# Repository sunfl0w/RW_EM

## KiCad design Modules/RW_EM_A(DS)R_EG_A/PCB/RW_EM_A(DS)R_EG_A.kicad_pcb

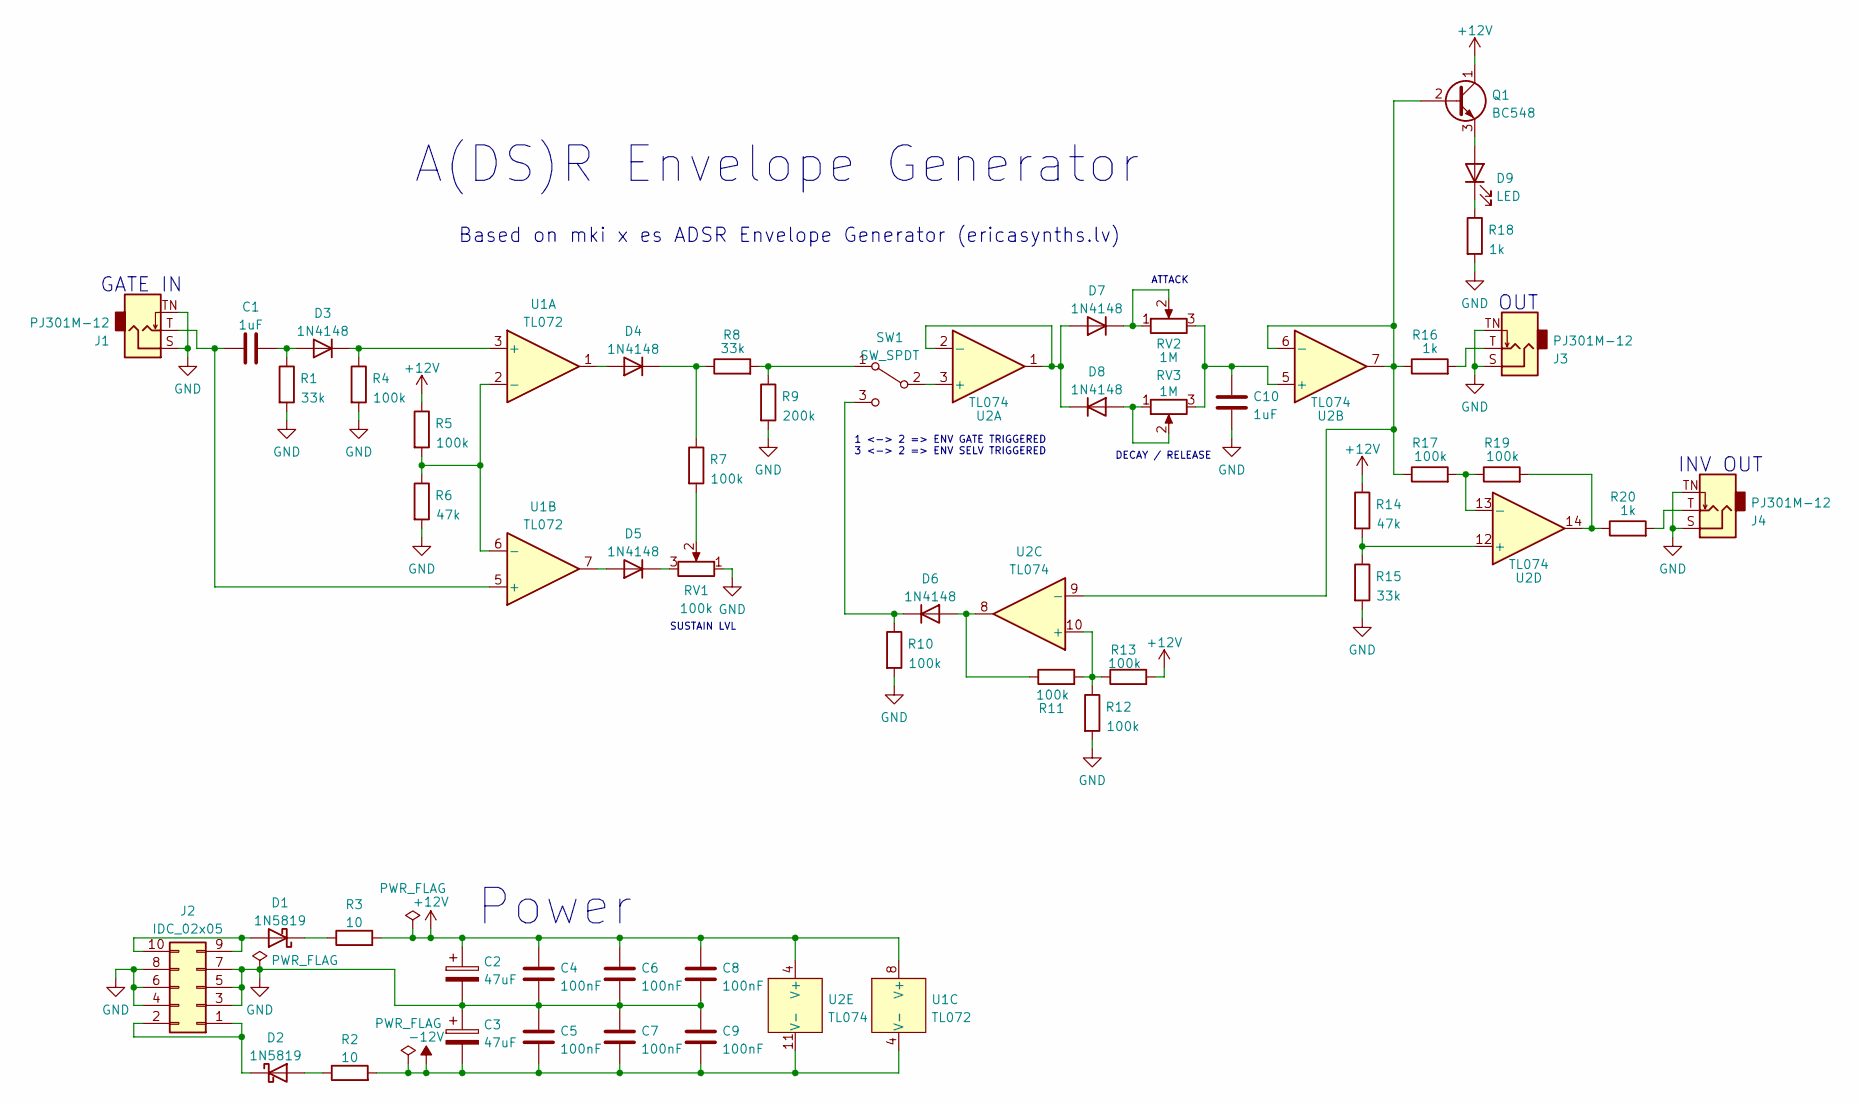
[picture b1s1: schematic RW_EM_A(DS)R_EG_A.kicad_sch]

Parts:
C1, C10: 1uF; C_Rect_L7.2mm_W3.5mm_P5.00mm_FKS2_FKP2_MKS2_MKP2
C2, C3: 47uF; CP_Radial_D5.0mm_P2.00mm
C4, C5, C6, C7, C8, C9: 100nF; C_Disc_D5.0mm_W2.5mm_P5.00mm
D1, D2: 1N5819; D_DO-41_SOD81_P10.16mm_Horizontal
D3, D4, D5, D6, D7, D8: 1N4148; D_DO-35_SOD27_P7.62mm_Horizontal
D9: LED; LED_D5.0mm
J1, J3, J4: PJ301M-12
J2: IDC_02x05; IDC-Header_2x05_P2.54mm_Vertical
Q1: BC548; TO-92_Inline
R1, R8, R15: 33k; R_Axial_DIN0207_L6.3mm_D2.5mm_P2.54mm_Vertical
R2, R3: 10; R_Axial_DIN0207_L6.3mm_D2.5mm_P10.16mm_Horizontal
R4, R5, R7, R10, R11, R12, R13, R17, R19: 100k; R_Axial_DIN0207_L6.3mm_D2.5mm_P2.54mm_Vertical
R6, R14: 47k; R_Axial_DIN0207_L6.3mm_D2.5mm_P2.54mm_Vertical
R9: 200k; R_Axial_DIN0207_L6.3mm_D2.5mm_P2.54mm_Vertical
R16, R18, R20: 1k; R_Axial_DIN0207_L6.3mm_D2.5mm_P10.16mm_Horizontal
RV1: 100k; Potentiometer_R0904N_SongHuei
RV2, RV3: 1M; Potentiometer_R0904N_SongHuei
SW1: SW_SPDT; Toggle_Switch_PINS_SPDT
U1: TL072; DIP-8_W7.62mm
U2: TL074; DIP-14_W7.62mm

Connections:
+12V: C2.1, C4.1, C6.1, C8.1, Q1.1 (C), R3.2, R5.1, R13.2, R14.1, U1.8 (V+), U2.4 (V+)
-12V: C3.2, C5.2, C7.2, C9.2, R2.2, U1.4 (V-), U2.11 (V-)
GND: C2.2, C3.1, C4.2, C5.1, C6.2, C7.1, C8.2, C9.1, C10.1, J1.S, J1.TN, J2.3, J2.4, J2.5, J2.6, J2.7, J2.8, J3.S, J3.TN, J4.S, J4.TN, R1.2, R4.2, R6.2, R9.2, R10.2, R12.2, R15.2, R18.2, RV1.1
unnamed: C1.1, J1.T, U1.5 (+)
unnamed: C1.2, D3.2 (A), R1.1
unnamed: C10.2, RV2.3, RV3.3, U2.5 (+)
unnamed: D1.1 (K), R3.1
unnamed: D1.2 (A), J2.9, J2.10
unnamed: D2.1 (K), J2.1, J2.2
unnamed: D2.2 (A), R2.1
unnamed: D3.1 (K), R4.1, U1.3 (+)
unnamed: D4.1 (K), R7.1, R8.1
unnamed: D4.2 (A), U1.1
unnamed: D5.1 (K), RV1.3
unnamed: D5.2 (A), U1.7
unnamed: D6.1 (K), R10.1, SW1.3 (C)
unnamed: D6.2 (A), R11.1, U2.8
unnamed: D7.1 (K), RV2.1, RV2.2
unnamed: D7.2 (A), D8.1 (K), U2.1, U2.2 (-)
unnamed: D8.2 (A), RV3.1, RV3.2
unnamed: D9.1 (K), R18.1
unnamed: D9.2 (A), Q1.3 (E)
unnamed: J3.T, R16.2
unnamed: J4.T, R20.2
unnamed: Q1.2 (B), R16.1, R17.1, U2.6 (-), U2.7, U2.9 (-)
unnamed: R5.2, R6.1, U1.2 (-), U1.6 (-)
unnamed: R7.2, RV1.2
unnamed: R8.2, R9.1, SW1.1 (A)
unnamed: R11.2, R12.1, R13.1, U2.10 (+)
unnamed: R14.2, R15.1, U2.12 (+)
unnamed: R17.2, R19.1, U2.13 (-)
unnamed: R19.2, R20.1, U2.14
unnamed: SW1.2 (B), U2.3 (+)

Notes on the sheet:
INV OUT
SUSTAIN LVL
1 <-> 2 => ENV GATE TRIGGERED 3 <-> 2 => ENV SELV TRIGGERED
OUT
A(DS)R Envelope Generator
DECAY / RELEASE
ATTACK
GATE IN
Based on mki x es ADSR Envelope Generator (ericasynths.lv)
Power

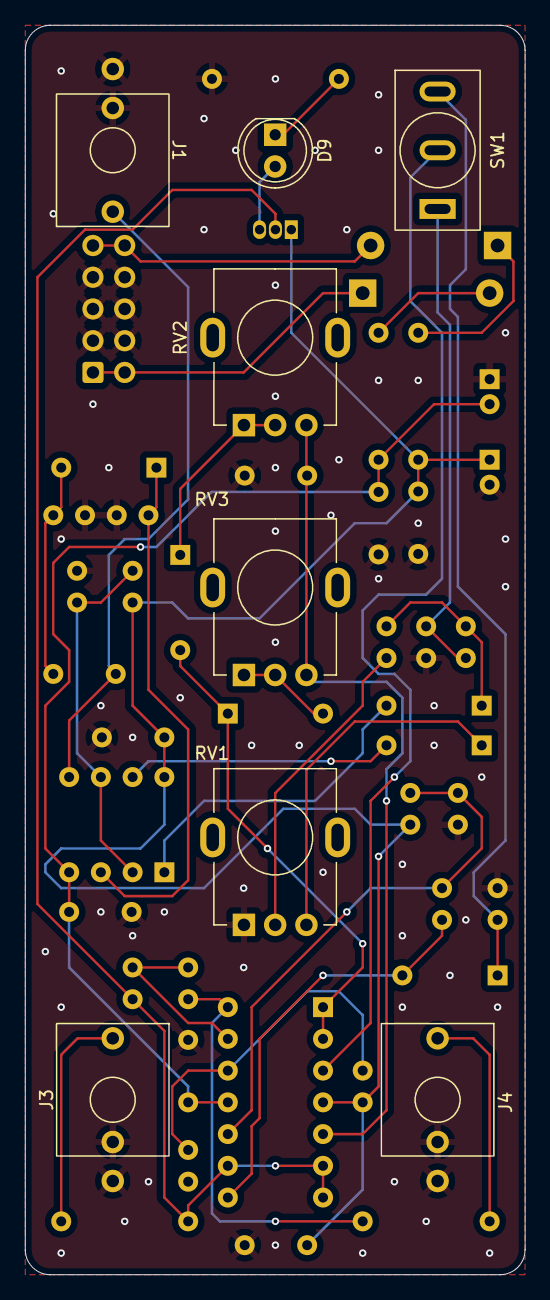
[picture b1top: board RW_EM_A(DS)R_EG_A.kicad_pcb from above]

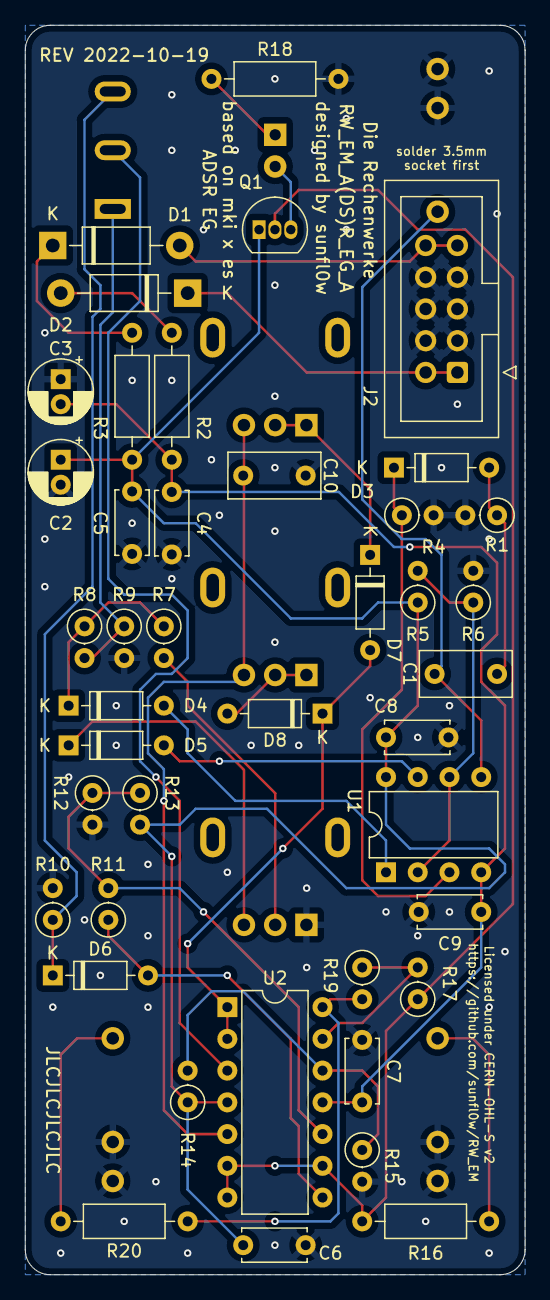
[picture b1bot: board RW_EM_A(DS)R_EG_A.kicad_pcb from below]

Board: 2 copper layers, 40.0 x 100.0 mm, 50 parts (42 on the bottom side), 33 nets.

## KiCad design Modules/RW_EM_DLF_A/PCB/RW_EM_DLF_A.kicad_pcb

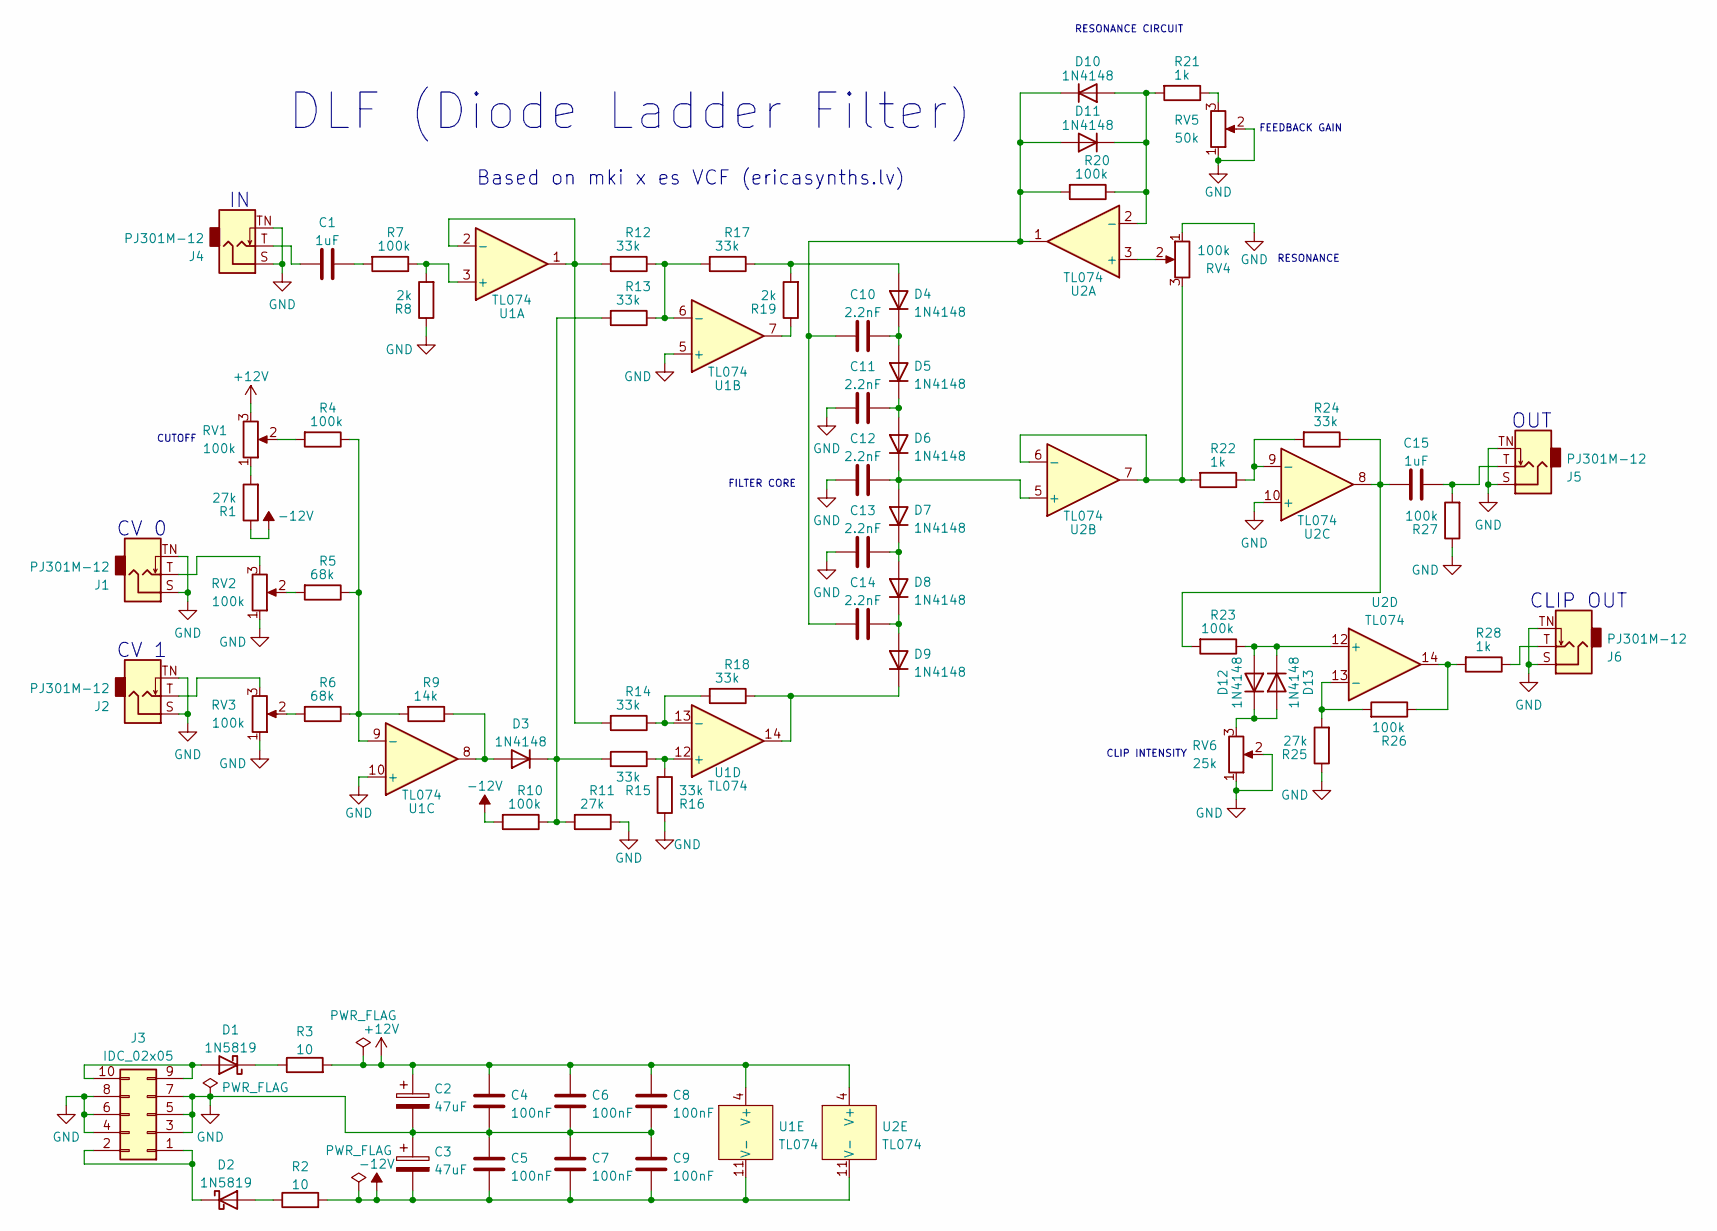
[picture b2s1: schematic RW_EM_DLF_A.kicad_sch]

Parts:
C1, C15: 1uF; C_Rect_L7.2mm_W4.5mm_P5.00mm_FKS2_FKP2_MKS2_MKP2
C2, C3: 47uF; CP_Radial_D5.0mm_P2.00mm
C4, C5, C6, C7, C8, C9: 100nF; C_Disc_D5.0mm_W2.5mm_P5.00mm
C10, C11, C12, C13, C14: 2.2nF; C_Rect_L7.2mm_W5.5mm_P5.00mm_FKS2_FKP2_MKS2_MKP2
D1, D2: 1N5819; D_DO-41_SOD81_P10.16mm_Horizontal
D3, D4, D5, D6, D7, D8, D9, D10, D11, D12, D13: 1N4148; D_DO-35_SOD27_P7.62mm_Horizontal
J1, J2, J4, J5, J6: PJ301M-12
J3: IDC_02x05; IDC-Header_2x05_P2.54mm_Vertical
R1, R11: 27k; R_Axial_DIN0207_L6.3mm_D2.5mm_P10.16mm_Horizontal
R2, R3: 10; R_Axial_DIN0207_L6.3mm_D2.5mm_P10.16mm_Horizontal
R4, R7, R20, R23, R26, R27: 100k; R_Axial_DIN0207_L6.3mm_D2.5mm_P2.54mm_Vertical
R5, R6: 68k; R_Axial_DIN0207_L6.3mm_D2.5mm_P2.54mm_Vertical
R8, R19: 2k; R_Axial_DIN0207_L6.3mm_D2.5mm_P2.54mm_Vertical
R9: 14k; R_Axial_DIN0207_L6.3mm_D2.5mm_P2.54mm_Vertical
R10: 100k; R_Axial_DIN0207_L6.3mm_D2.5mm_P10.16mm_Horizontal
R12, R13, R17, R24: 33k; R_Axial_DIN0207_L6.3mm_D2.5mm_P2.54mm_Vertical
R14, R15, R16, R18: 33k; R_Axial_DIN0207_L6.3mm_D2.5mm_P10.16mm_Horizontal
R21, R22, R28: 1k; R_Axial_DIN0207_L6.3mm_D2.5mm_P2.54mm_Vertical
R25: 27k; R_Axial_DIN0207_L6.3mm_D2.5mm_P2.54mm_Vertical
RV1: 100k; Potentiometer_Alpha_RD901F-40-00D_Single_Vertical
RV2, RV3, RV4: 100k; Potentiometer_R0904N_SongHuei
RV5: 50k; Potentiometer_R0904N_SongHuei
RV6: 25k; Potentiometer_R0904N_SongHuei
U1, U2: TL074

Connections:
+12V: C2.1, C4.1, C6.1, C8.1, R3.2, RV1.3, U1.4 (V+), U2.4 (V+)
-12V: C3.2, C5.2, C7.2, C9.2, R1.1, R2.2, R10.2, U1.11 (V-), U2.11 (V-)
GND: C2.2, C3.1, C4.2, C5.1, C6.2, C7.1, C8.2, C9.1, C11.1, C12.1, C13.1, J1.S, J1.TN, J2.S, J2.TN, J3.3, J3.4, J3.5, J3.6, J3.7, J3.8, J4.S, J4.TN, J5.S, J5.TN, J6.S, J6.TN, R8.1, R11.1, R16.1, R25.1, R27.1, RV2.1, RV3.1, RV4.1, RV5.1, RV5.2, RV6.1, RV6.2, U1.5 (+), U1.10 (+), U2.10 (+)
unnamed: C1.1, J4.T
unnamed: C1.2, R7.2
unnamed: C10.1, C14.1, D10.1 (K), D11.2 (A), R20.2, U2.1
unnamed: C10.2, D4.1 (K), D5.2 (A)
unnamed: C11.2, D5.1 (K), D6.2 (A)
unnamed: C12.2, D6.1 (K), D7.2 (A), U2.5 (+)
unnamed: C13.2, D7.1 (K), D8.2 (A)
unnamed: C14.2, D8.1 (K), D9.2 (A)
unnamed: C15.1, R23.2, R24.1, U2.8
unnamed: C15.2, J5.T, R27.2
unnamed: D1.1 (K), R3.1
unnamed: D1.2 (A), J3.9, J3.10
unnamed: D2.1 (K), J3.1, J3.2
unnamed: D2.2 (A), R2.1
unnamed: D3.1 (K), R10.1, R11.2, R13.2, R15.2
unnamed: D3.2 (A), R9.1, U1.8
unnamed: D4.2 (A), R17.1, R19.2
unnamed: D9.1 (K), R18.1, U1.14
unnamed: D10.2 (A), D11.1 (K), R20.1, R21.2, U2.2 (-)
unnamed: D12.1 (K), D13.2 (A), RV6.3
unnamed: D12.2 (A), D13.1 (K), R23.1, U2.12 (+)
unnamed: J1.T, RV2.3
unnamed: J2.T, RV3.3
unnamed: J6.T, R28.1
unnamed: R1.2, RV1.1
unnamed: R4.1, R5.1, R6.1, R9.2, U1.9 (-)
unnamed: R4.2, RV1.2
unnamed: R5.2, RV2.2
unnamed: R6.2, RV3.2
unnamed: R7.1, R8.2, U1.3 (+)
unnamed: R12.1, R13.1, R17.2, U1.6 (-)
unnamed: R12.2, R14.2, U1.1, U1.2 (-)
unnamed: R14.1, R18.2, U1.13 (-)
unnamed: R15.1, R16.2, U1.12 (+)
unnamed: R19.1, U1.7
unnamed: R21.1, RV5.3
unnamed: R22.1, R24.2, U2.9 (-)
unnamed: R22.2, RV4.3, U2.6 (-), U2.7
unnamed: R25.2, R26.2, U2.13 (-)
unnamed: R26.1, R28.2, U2.14
unnamed: RV4.2, U2.3 (+)

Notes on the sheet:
CLIP OUT
FEEDBACK GAIN
CV 1
CV 0
CLIP INTENSITY
FILTER CORE
RESONANCE CIRCUIT
RESONANCE
Based on mki x es VCF (ericasynths.lv)
DLF (Diode Ladder Filter)
CUTOFF
OUT

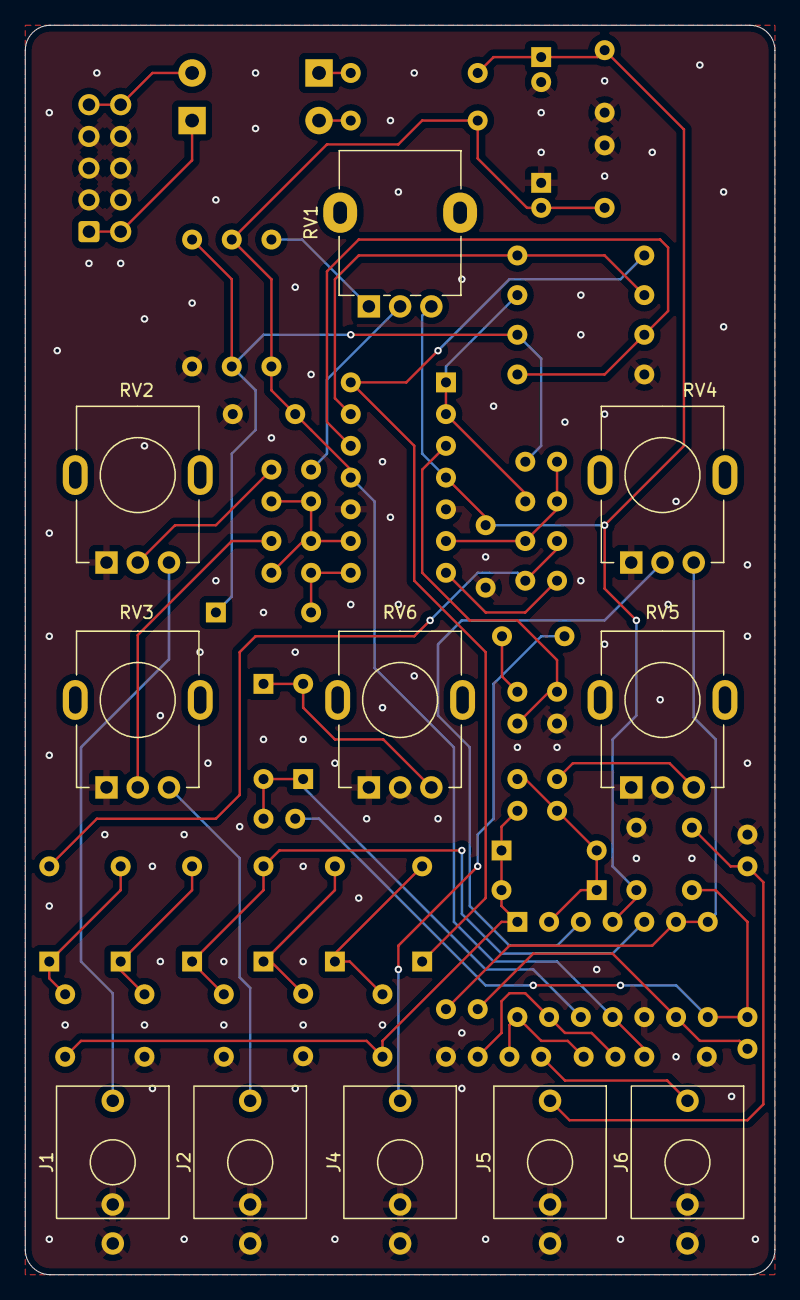
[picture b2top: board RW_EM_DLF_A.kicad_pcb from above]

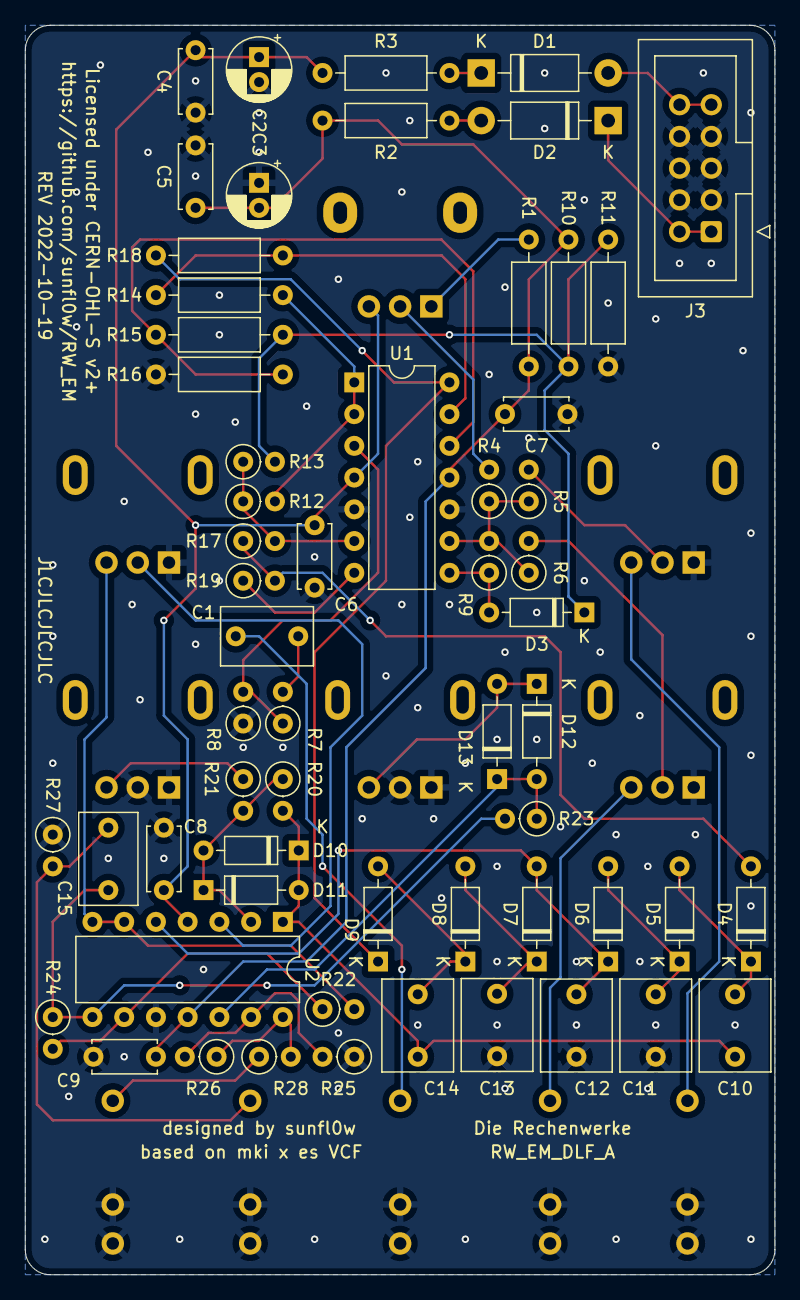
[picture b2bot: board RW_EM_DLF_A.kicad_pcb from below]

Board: 2 copper layers, 60.0 x 100.0 mm, 70 parts (59 on the bottom side), 44 nets.

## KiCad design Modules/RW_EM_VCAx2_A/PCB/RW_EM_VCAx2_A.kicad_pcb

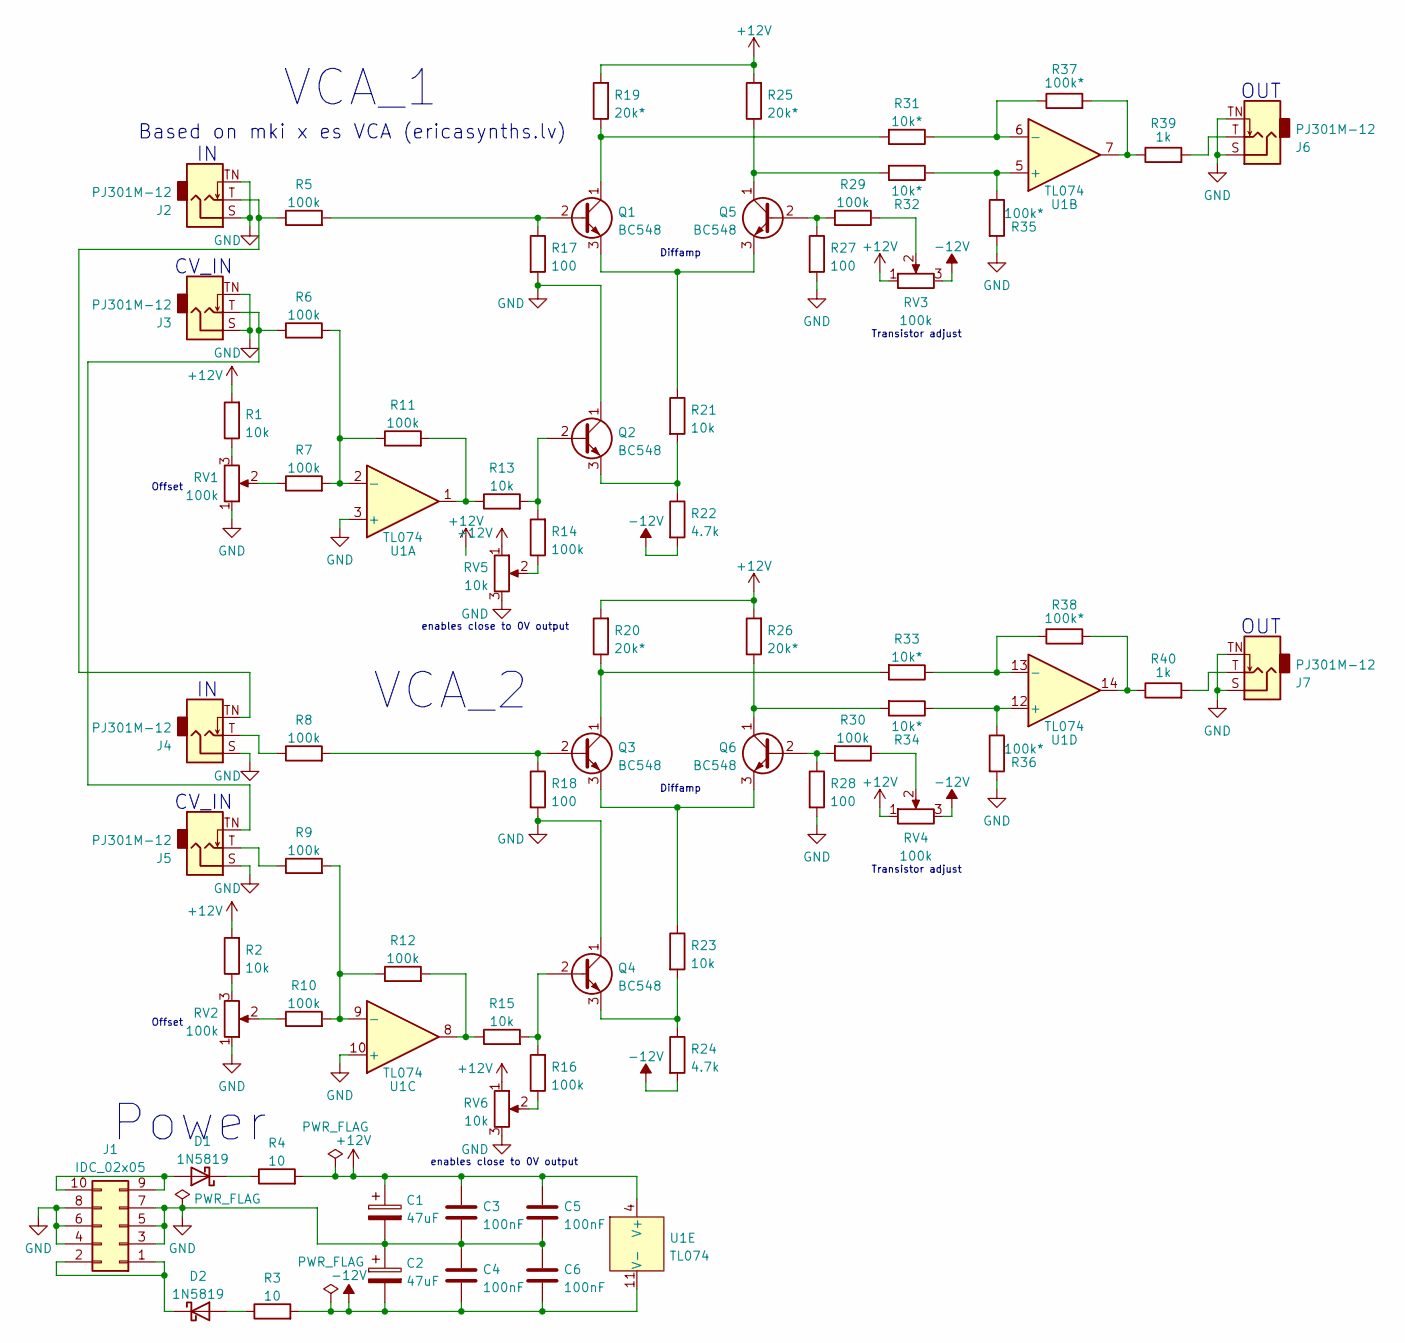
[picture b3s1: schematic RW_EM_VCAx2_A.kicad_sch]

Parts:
C1, C2: 47uF; CP_Radial_D5.0mm_P2.00mm
C3, C4, C5, C6: 100nF; C_Disc_D5.0mm_W2.5mm_P5.00mm
D1, D2: 1N5819; D_DO-41_SOD81_P10.16mm_Horizontal
J1: IDC_02x05; IDC-Header_2x05_P2.54mm_Vertical
J2, J3, J4, J5, J6, J7: PJ301M-12
Q1, Q2, Q3, Q4, Q5, Q6: BC548; TO-92_Inline
R1, R2, R13, R15, R21, R23: 10k; R_Axial_DIN0207_L6.3mm_D2.5mm_P2.54mm_Vertical
R3, R4: 10; R_Axial_DIN0207_L6.3mm_D2.5mm_P10.16mm_Horizontal
R5, R6, R7, R8, R9, R10, R11, R12, R14, R16, R29, R30: 100k; R_Axial_DIN0207_L6.3mm_D2.5mm_P2.54mm_Vertical
R17, R18, R27, R28: 100; R_Axial_DIN0207_L6.3mm_D2.5mm_P2.54mm_Vertical
R19, R20, R25, R26: 20k*; R_Axial_DIN0207_L6.3mm_D2.5mm_P2.54mm_Vertical
R22, R24: 4.7k; R_Axial_DIN0207_L6.3mm_D2.5mm_P2.54mm_Vertical
R31, R32, R33, R34: 10k*; R_Axial_DIN0207_L6.3mm_D2.5mm_P2.54mm_Vertical
R35, R36, R37, R38: 100k*; R_Axial_DIN0207_L6.3mm_D2.5mm_P2.54mm_Vertical
R39, R40: 1k; R_Axial_DIN0207_L6.3mm_D2.5mm_P2.54mm_Vertical
RV1, RV2: 100k; Potentiometer_R0904N_SongHuei
RV3, RV4: 100k; Potentiometer_Bourns_3296W_Vertical
RV5, RV6: 10k; Potentiometer_Bourns_3296W_Vertical
U1: TL074; DIP-14_W7.62mm

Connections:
+12V: C1.1, C3.1, C5.1, R1.2, R2.2, R4.2, R19.2, R20.2, R25.2, R26.2, RV3.1, RV4.1, RV5.1, RV6.1, U1.4 (V+)
-12V: C2.2, C4.2, C6.2, R3.2, R22.2, R24.2, RV3.3, RV4.3, U1.11 (V-)
GND: C1.2, C2.1, C3.2, C4.1, C5.2, C6.1, J1.3, J1.4, J1.5, J1.6, J1.7, J1.8, J2.S, J2.TN, J3.S, J3.TN, J4.S, J5.S, J6.S, J6.TN, J7.S, J7.TN, Q2.1 (C), Q4.1 (C), R17.2, R18.2, R27.2, R28.2, R35.2, R36.2, RV1.1, RV2.1, RV5.3, RV6.3, U1.3 (+), U1.10 (+)
unnamed: D1.1 (K), R4.1
unnamed: D1.2 (A), J1.9, J1.10
unnamed: D2.1 (K), J1.1, J1.2
unnamed: D2.2 (A), R3.1
unnamed: J2.T, J4.TN, R5.1
unnamed: J3.T, J5.TN, R6.1
unnamed: J4.T, R8.1
unnamed: J5.T, R9.1
unnamed: J6.T, R39.2
unnamed: J7.T, R40.2
unnamed: Q1.1 (C), R19.1, R31.2
unnamed: Q1.2 (B), R5.2, R17.1
unnamed: Q1.3 (E), Q5.3 (E), R21.1
unnamed: Q2.2 (B), R13.2, R14.2
unnamed: Q2.3 (E), R21.2, R22.1
unnamed: Q3.1 (C), R20.1, R33.2
unnamed: Q3.2 (B), R8.2, R18.1
unnamed: Q3.3 (E), Q6.3 (E), R23.1
unnamed: Q4.2 (B), R15.2, R16.2
unnamed: Q4.3 (E), R23.2, R24.1
unnamed: Q5.1 (C), R25.1, R32.2
unnamed: Q5.2 (B), R27.1, R29.2
unnamed: Q6.1 (C), R26.1, R34.2
unnamed: Q6.2 (B), R28.1, R30.2
unnamed: R1.1, RV1.3
unnamed: R2.1, RV2.3
unnamed: R7.1, RV1.2
unnamed: R10.1, RV2.2
unnamed: R9.2, R10.2, R12.1, U1.9 (-)
unnamed: R6.2, R7.2, R11.1, U1.2 (-)
unnamed: R11.2, R13.1, U1.1
unnamed: R12.2, R15.1, U1.8
unnamed: R14.1, RV5.2
unnamed: R16.1, RV6.2
unnamed: R29.1, RV3.2
unnamed: R30.1, RV4.2
unnamed: R31.1, R37.1, U1.6 (-)
unnamed: R32.1, R35.1, U1.5 (+)
unnamed: R33.1, R38.1, U1.13 (-)
unnamed: R34.1, R36.1, U1.12 (+)
unnamed: R37.2, R39.1, U1.7
unnamed: R38.2, R40.1, U1.14

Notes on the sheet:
Offset
Diffamp
Power
OUT
Based on mki x es VCA (ericasynths.lv)
VCA_1
CV_IN
Transistor adjust
enables close to 0V output
VCA_2

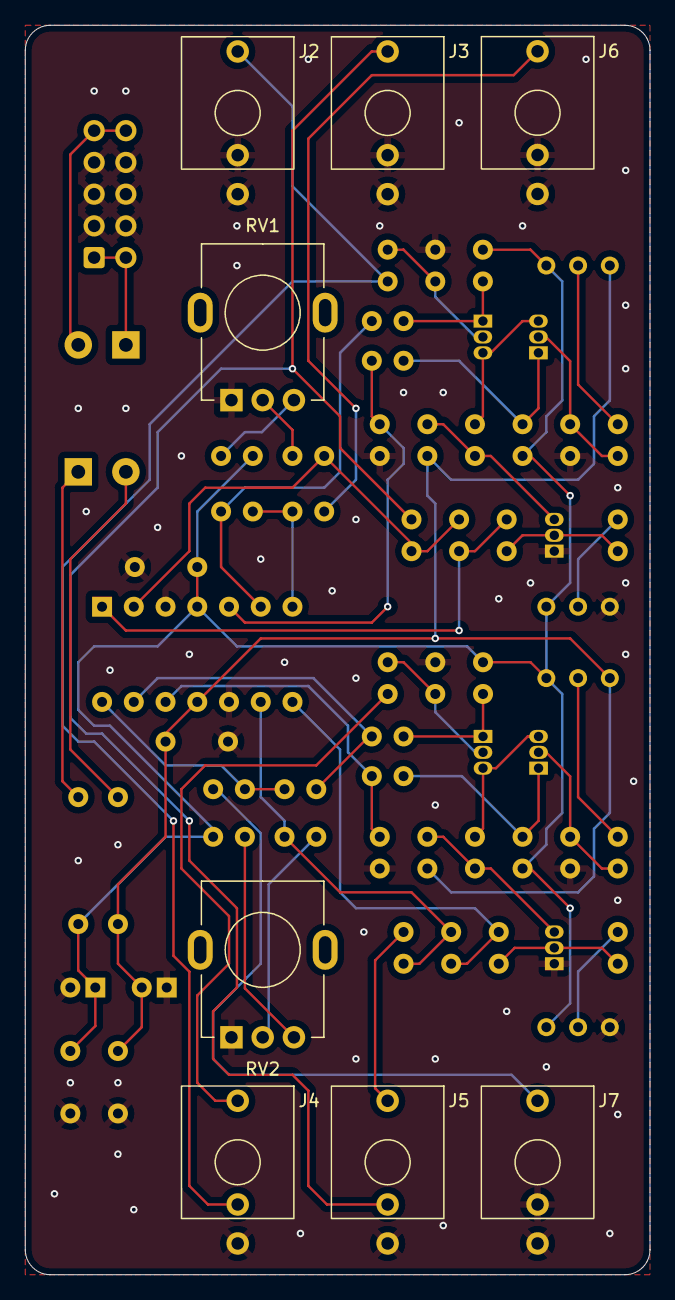
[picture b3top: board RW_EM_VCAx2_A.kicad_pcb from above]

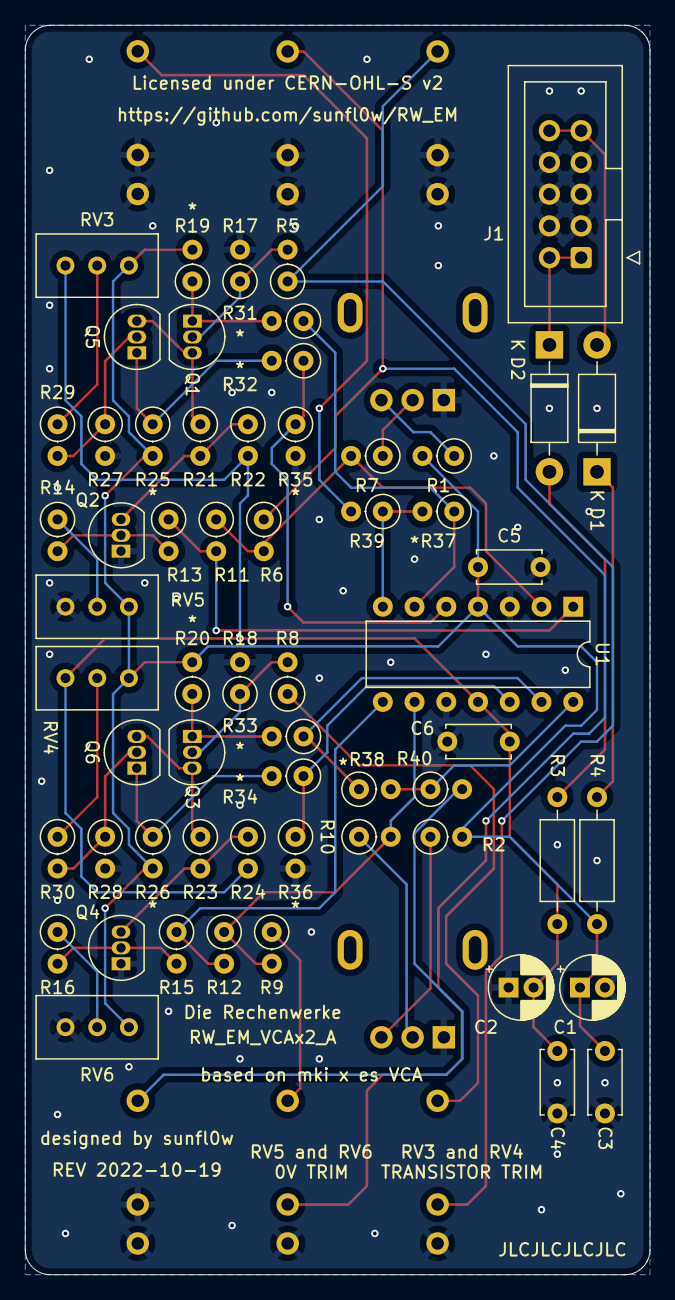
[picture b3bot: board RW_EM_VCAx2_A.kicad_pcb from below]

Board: 2 copper layers, 50.0 x 100.0 mm, 68 parts (60 on the bottom side), 45 nets.

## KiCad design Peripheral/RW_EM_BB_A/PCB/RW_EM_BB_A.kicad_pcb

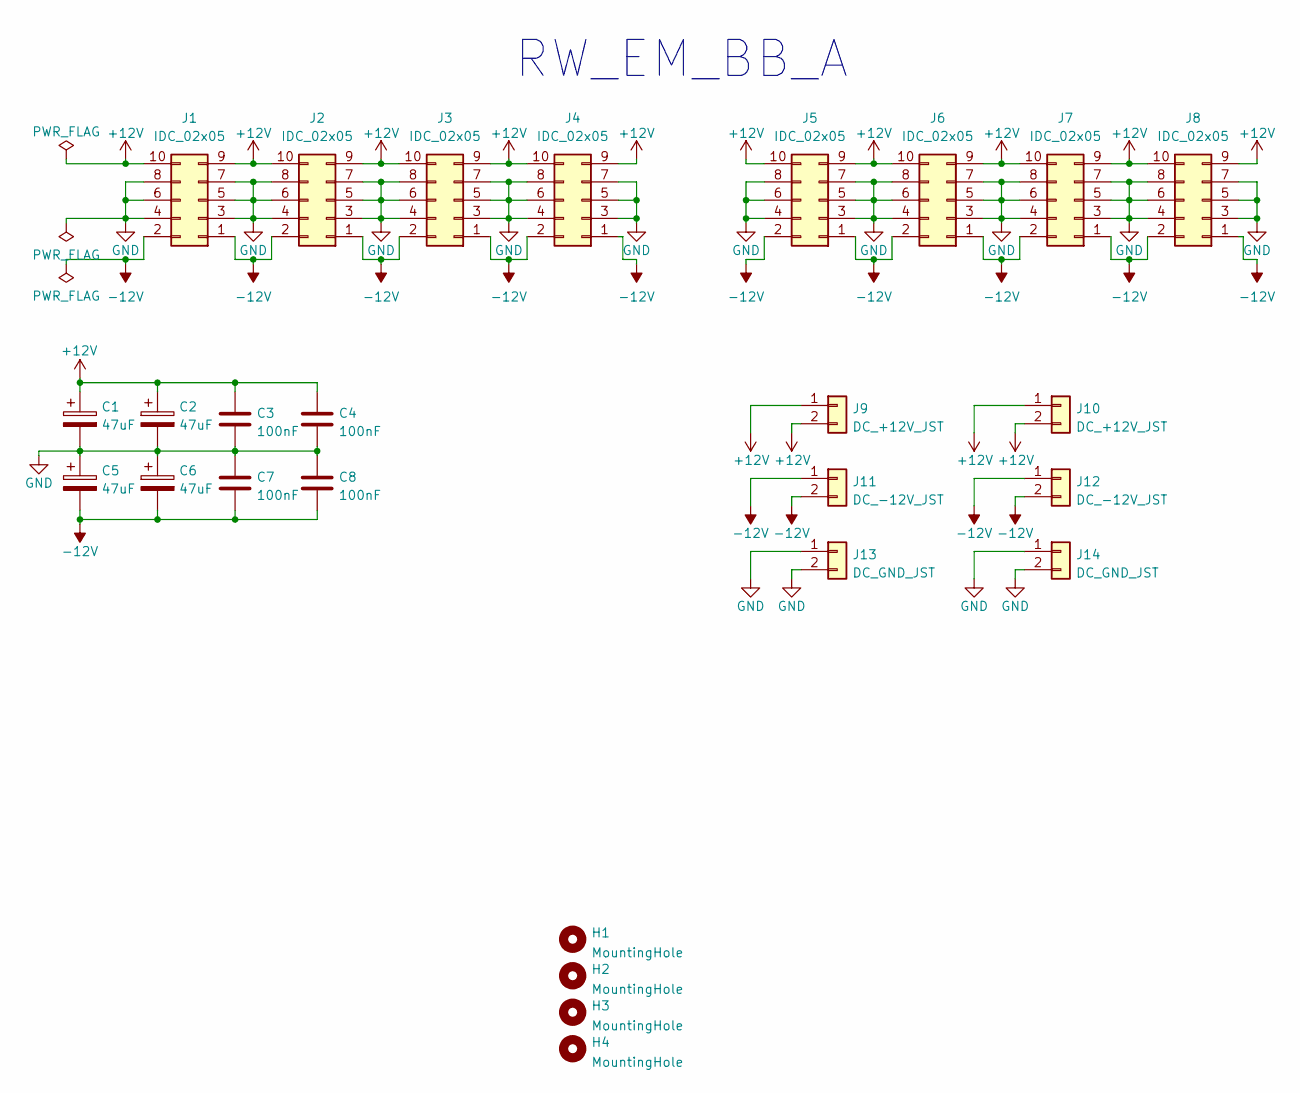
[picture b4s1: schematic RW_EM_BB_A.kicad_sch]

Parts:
C1, C2, C5, C6: 47uF; CP_Radial_D5.0mm_P2.00mm
C3, C4, C7, C8: 100nF; C_Disc_D5.0mm_W2.5mm_P5.00mm
H1, H2, H3, H4: MountingHole; MountingHole_3.2mm_M3
J1, J2, J3, J4, J5, J6, J7, J8: IDC_02x05; IDC-Header_2x05_P2.54mm_Vertical
J9, J10: DC_+12V_JST; JST_XH_B2B-XH-A_1x02_P2.50mm_Vertical
J11, J12: DC_-12V_JST; JST_XH_B2B-XH-A_1x02_P2.50mm_Vertical
J13, J14: DC_GND_JST; JST_XH_B2B-XH-A_1x02_P2.50mm_Vertical

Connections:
+12V: C1.1, C2.1, C3.1, C4.1, J1.9, J1.10, J2.9, J2.10, J3.9, J3.10, J4.9, J4.10, J5.9, J5.10, J6.9, J6.10, J7.9, J7.10, J8.9, J8.10, J9.1, J9.2, J10.1, J10.2
-12V: C5.2, C6.2, C7.2, C8.2, J1.1, J1.2, J2.1, J2.2, J3.1, J3.2, J4.1, J4.2, J5.1, J5.2, J6.1, J6.2, J7.1, J7.2, J8.1, J8.2, J11.1, J11.2, J12.1, J12.2
GND: C1.2, C2.2, C3.2, C4.2, C5.1, C6.1, C7.1, C8.1, J1.3, J1.4, J1.5, J1.6, J1.7, J1.8, J2.3, J2.4, J2.5, J2.6, J2.7, J2.8, J3.3, J3.4, J3.5, J3.6, J3.7, J3.8, J4.3, J4.4, J4.5, J4.6, J4.7, J4.8, J5.3, J5.4, J5.5, J5.6, J5.7, J5.8, J6.3, J6.4, J6.5, J6.6, J6.7, J6.8, J7.3, J7.4, J7.5, J7.6, J7.7, J7.8, J8.3, J8.4, J8.5, J8.6, J8.7, J8.8, J13.1, J13.2, J14.1, J14.2

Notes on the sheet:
RW_EM_BB_A

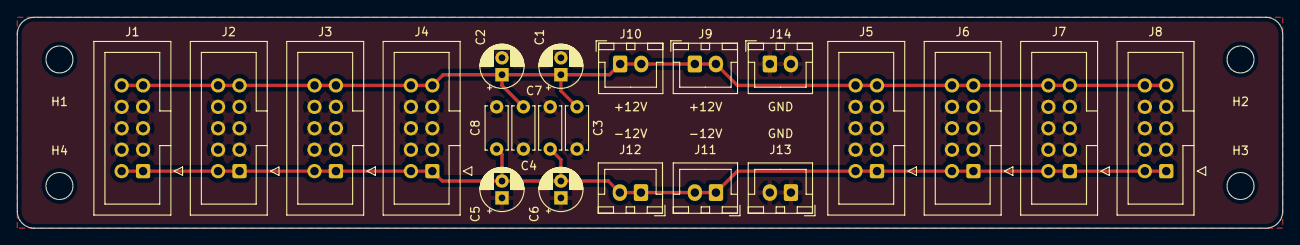
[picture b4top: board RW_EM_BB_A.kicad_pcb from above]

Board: 2 copper layers, 150.0 x 25.0 mm, 26 parts (0 on the bottom side), 3 nets.

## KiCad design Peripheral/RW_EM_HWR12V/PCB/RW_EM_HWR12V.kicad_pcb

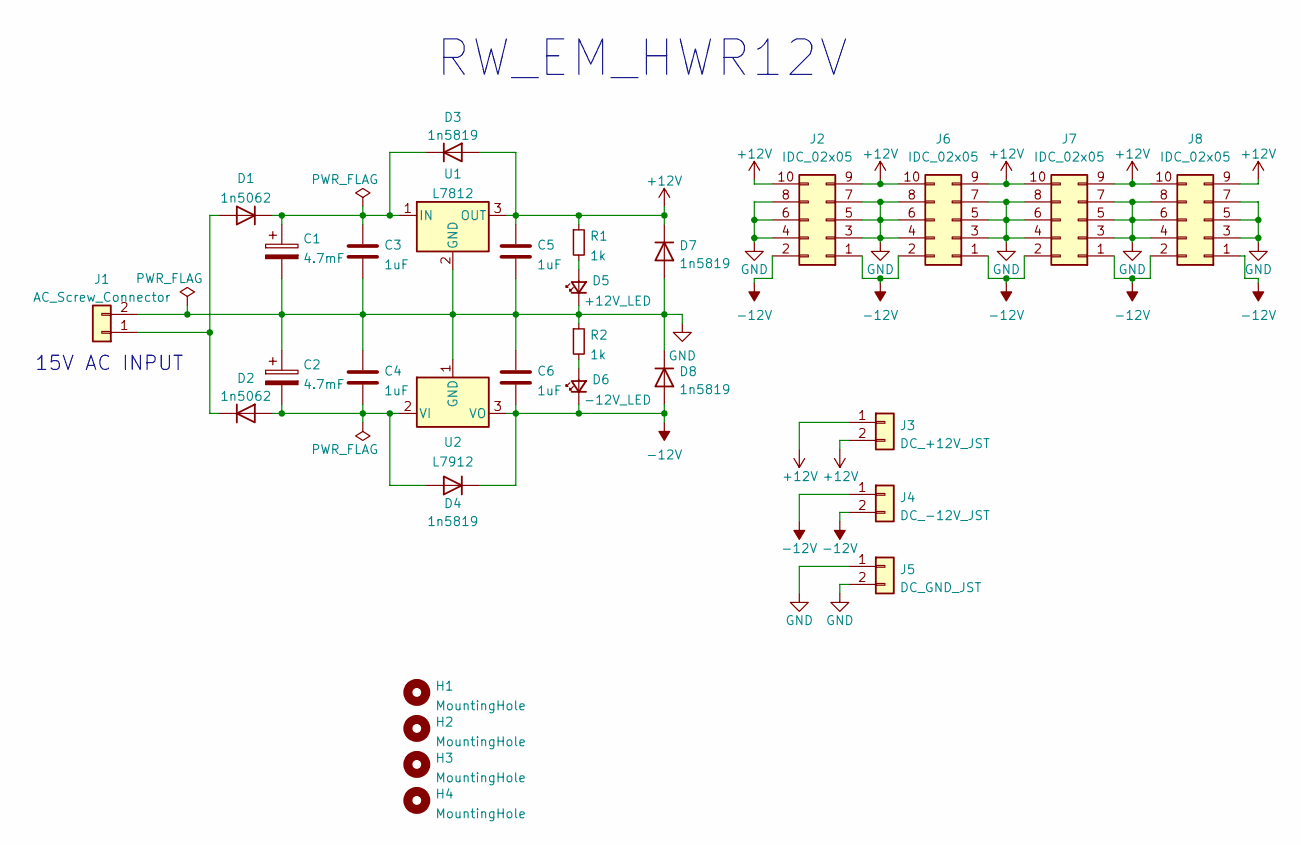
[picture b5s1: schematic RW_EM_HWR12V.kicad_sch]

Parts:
C1, C2: 4.7mF; CP_Radial_D18.0mm_P7.50mm
C3, C4, C5, C6: 1uF; C_Disc_D4.7mm_W2.5mm_P5.00mm
D1, D2: 1n5062; D_DO-15_P10.16mm_Horizontal
D3, D4, D7, D8: 1n5819; D_DO-41_SOD81_P10.16mm_Horizontal
D5: +12V_LED; LED_D5.0mm
D6: -12V_LED; LED_D5.0mm
H1, H2, H3, H4: MountingHole; MountingHole_3.2mm_M3
J1: AC_Screw_Connector; TerminalBlock_MetzConnect_Type101_RT01602HBWC_1x02_P5.08mm_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
J2, J6, J7, J8: IDC_02x05; IDC-Header_2x05_P2.54mm_Vertical
J3: DC_+12V_JST; JST_XH_B2B-XH-A_1x02_P2.50mm_Vertical
J4: DC_-12V_JST; JST_XH_B2B-XH-A_1x02_P2.50mm_Vertical
J5: DC_GND_JST; JST_XH_B2B-XH-A_1x02_P2.50mm_Vertical
R1, R2: 1k; R_Axial_DIN0207_L6.3mm_D2.5mm_P10.16mm_Horizontal
U1: L7812; TO-220-3_Vertical
U2: L7912; TO-220-3_Vertical

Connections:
+12V: C5.1, D3.2 (A), D7.1 (K), J2.9, J2.10, J3.1, J3.2, J6.9, J6.10, J7.9, J7.10, J8.9, J8.10, R1.1, U1.3 (OUT)
-12V: C6.2, D4.1 (K), D6.1 (K), D8.2 (A), J2.1, J2.2, J4.1, J4.2, J6.1, J6.2, J7.1, J7.2, J8.1, J8.2, U2.3 (VO)
GND: C1.2, C2.1, C3.2, C4.1, C5.2, C6.1, D5.1 (K), D7.2 (A), D8.1 (K), J1.2, J2.3, J2.4, J2.5, J2.6, J2.7, J2.8, J5.1, J5.2, J6.3, J6.4, J6.5, J6.6, J6.7, J6.8, J7.3, J7.4, J7.5, J7.6, J7.7, J7.8, J8.3, J8.4, J8.5, J8.6, J8.7, J8.8, R2.1, U1.2 (GND), U2.1 (GND)
unnamed: C1.1, C3.1, D1.1 (K), D3.1 (K), U1.1 (IN)
unnamed: C2.2, C4.2, D2.2 (A), D4.2 (A), U2.2 (VI)
unnamed: D1.2 (A), D2.1 (K), J1.1
unnamed: D5.2 (A), R1.2
unnamed: D6.2 (A), R2.2

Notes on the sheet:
15V AC INPUT
RW_EM_HWR12V

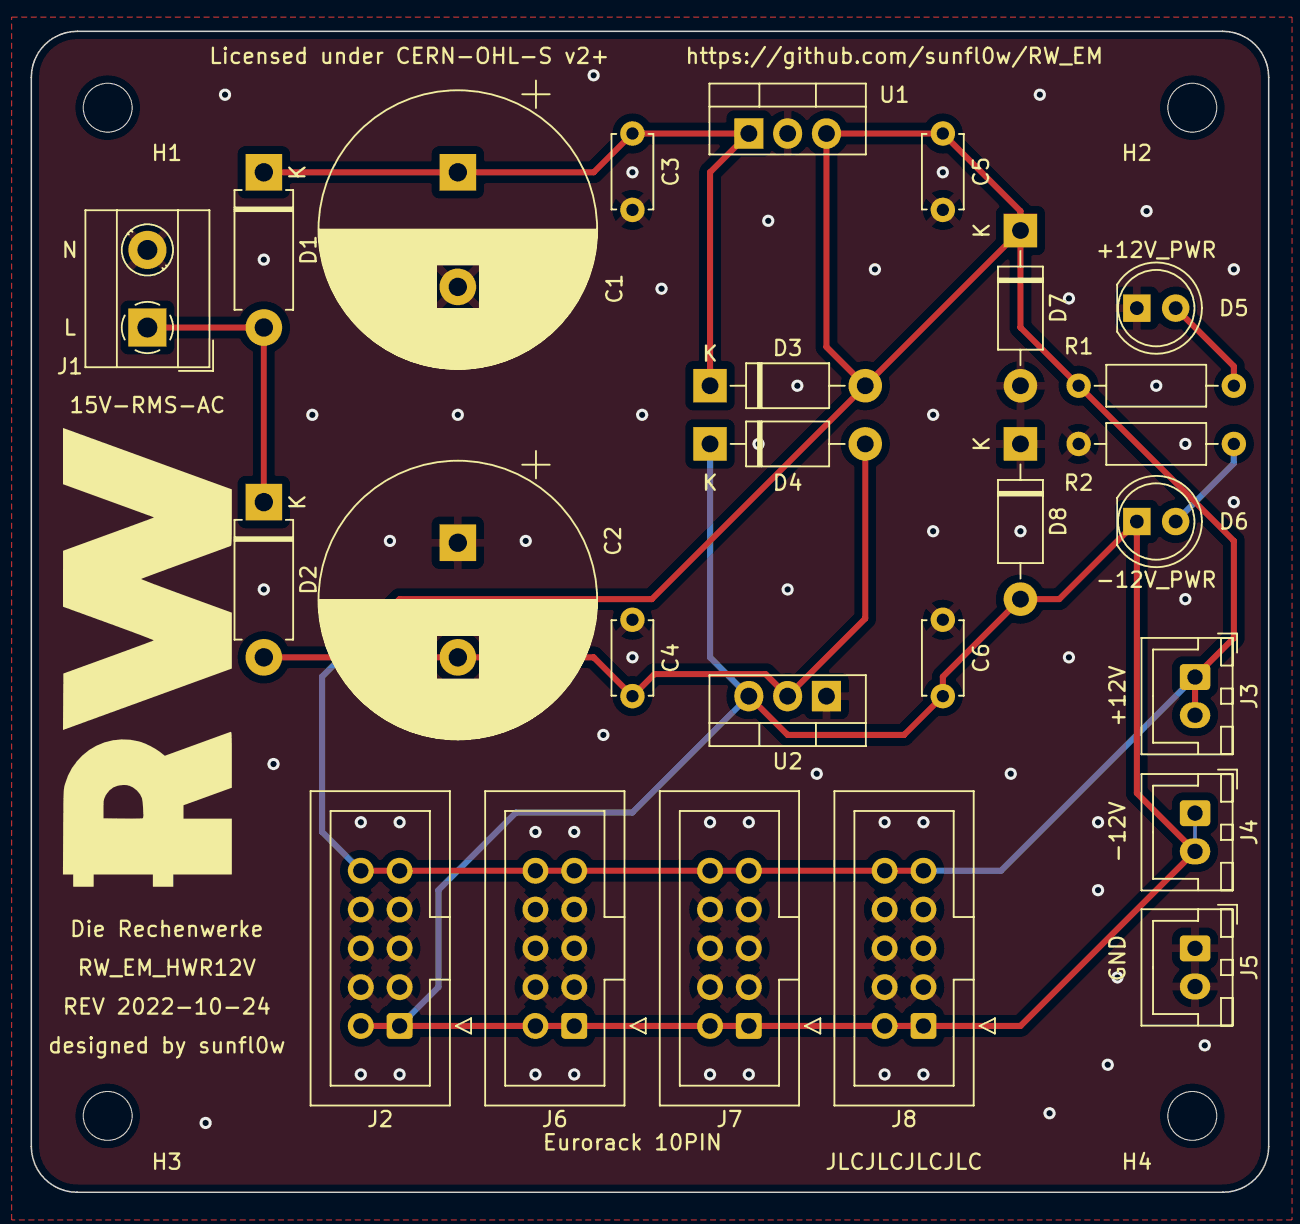
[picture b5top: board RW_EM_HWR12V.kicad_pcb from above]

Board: 2 copper layers, 81.0 x 76.0 mm, 30 parts (0 on the bottom side), 8 nets.

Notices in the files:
Modules/RW_EM_A(DS)R_EG_A/PCB/RW_EM_A(DS)R_EG_A.kicad_pcb:
Licensed under CERN-OHL-S v2+
